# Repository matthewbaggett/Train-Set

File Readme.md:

Layout shape:
 * 1300mm x 550mm
 
Cutting List:
 * Batons 34mm x 44mm x <n>mm:
   * A: 4x 550mm 
   * B: 2x 416mm
   * C: 1x 405mm
   * D: 2x 276mm
   * E: 2x 256mm
   * F: 2x 182mm
   * Cut A1-3 and B1 from length 1, remainder from length 2, then F1-2 from length 3, if using 210cm
   
Parts list:
 * Base board: 5.5mm thick ply https://www.praxis.nl/bouwmaterialen/hout/multiplex/powerplex-lite-en-636-1-svlk-244x122-cm-5-5-mm/5589211#specs
 * Batons: 
   * either 2x: 34mm x 44mm x 2700mm Spruce https://www.praxis.nl/bouwmaterialen/hout/timmerhout/schaaflat-vuren-34-x-34mm-270cm/5162845
   * or 3x: 34mm x 44mm x 2100cm Spruce https://www.praxis.nl/bouwmaterialen/hout/timmerhout/schaaflat-vuren-34x44mm-210cm/0482950
 * Drill bits: https://www.praxis.nl/gereedschap-installatiemateriaal/elektrisch-gereedschap/accessoires/boor-en-bitsets/makita-42-delige-bitset-p-45272/5460553
 * 20mm drill bit: https://www.praxis.nl/gereedschap-installatiemateriaal/elektrisch-gereedschap/accessoires/boren/stanley-speedboor-20mm/5287960

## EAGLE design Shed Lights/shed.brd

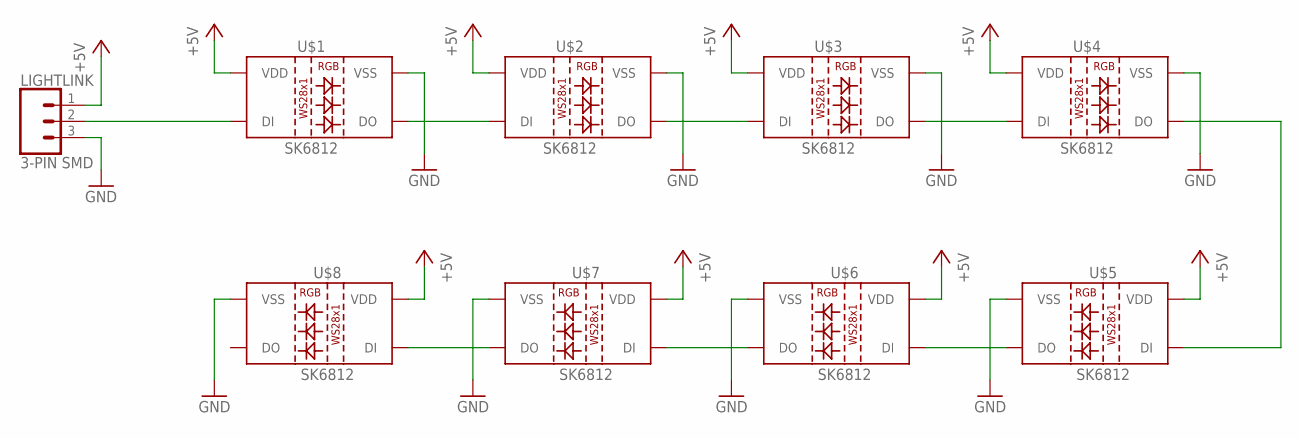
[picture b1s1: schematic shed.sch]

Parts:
LIGHTLINK: 3-PIN SMD; JST-3-SMD
U$1, U$2, U$3, U$4, U$5, U$6, U$7, U$8: SK6812; LED3535

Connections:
+5V: LIGHTLINK.1 (3), U$1.3 (VDD), U$2.3 (VDD), U$3.3 (VDD), U$4.3 (VDD), U$5.3 (VDD), U$6.3 (VDD), U$7.3 (VDD), U$8.3 (VDD)
GND: LIGHTLINK.3 (1), U$1.1 (VSS), U$2.1 (VSS), U$3.1 (VSS), U$4.1 (VSS), U$5.1 (VSS), U$6.1 (VSS), U$7.1 (VSS), U$8.1 (VSS)
unnamed: U$2.4 (DO), U$3.2 (DI)
unnamed: U$3.4 (DO), U$4.2 (DI)
unnamed: U$1.4 (DO), U$2.2 (DI)
unnamed: LIGHTLINK.2, U$1.2 (DI)
unnamed: U$5.4 (DO), U$6.2 (DI)
unnamed: U$4.4 (DO), U$5.2 (DI)
unnamed: U$6.4 (DO), U$7.2 (DI)
unnamed: U$7.4 (DO), U$8.2 (DI)

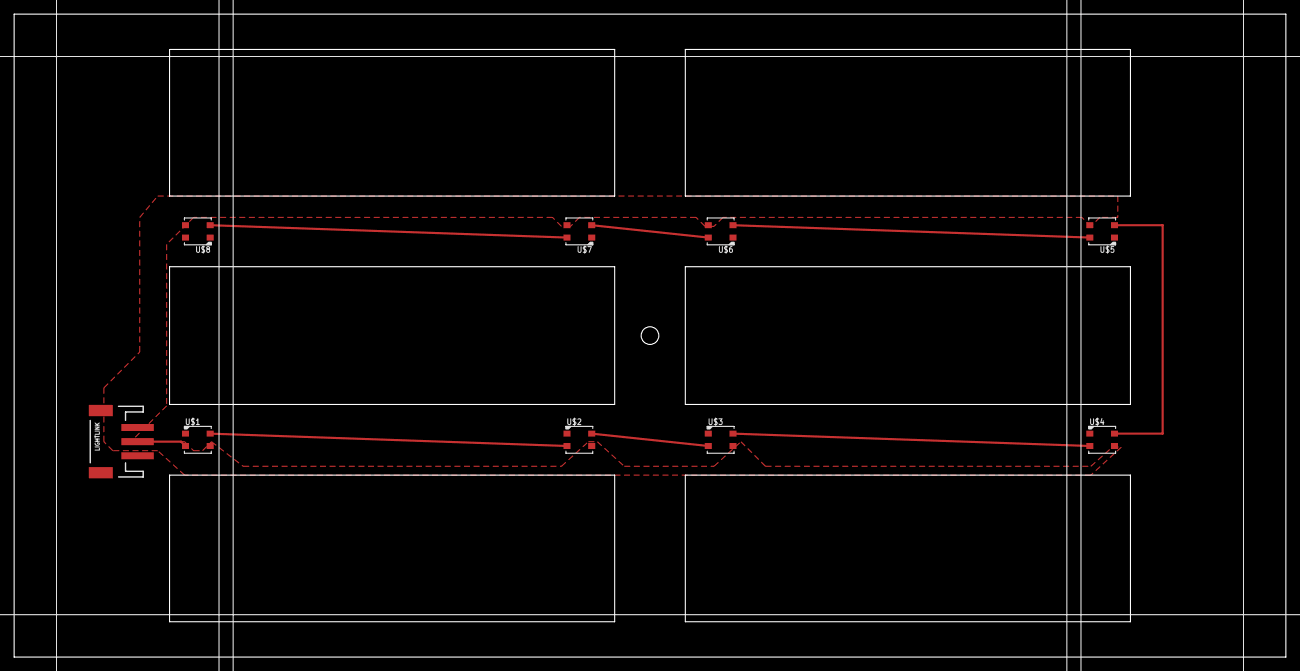
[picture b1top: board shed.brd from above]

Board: 2 copper layers, 180.0 x 91.0 mm, 9 parts (0 on the bottom side), 10 nets.

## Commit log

2020-03-18 Initial plan in anyrail
2020-03-18 More planning
2020-03-18 Initial shed LED PCB

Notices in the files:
parts and their libraries:
SparkFun-Connectors: Licensing: Creative Commons ShareAlike 4.0 International - https://creativecommons.org/licenses/by-sa/4.0
